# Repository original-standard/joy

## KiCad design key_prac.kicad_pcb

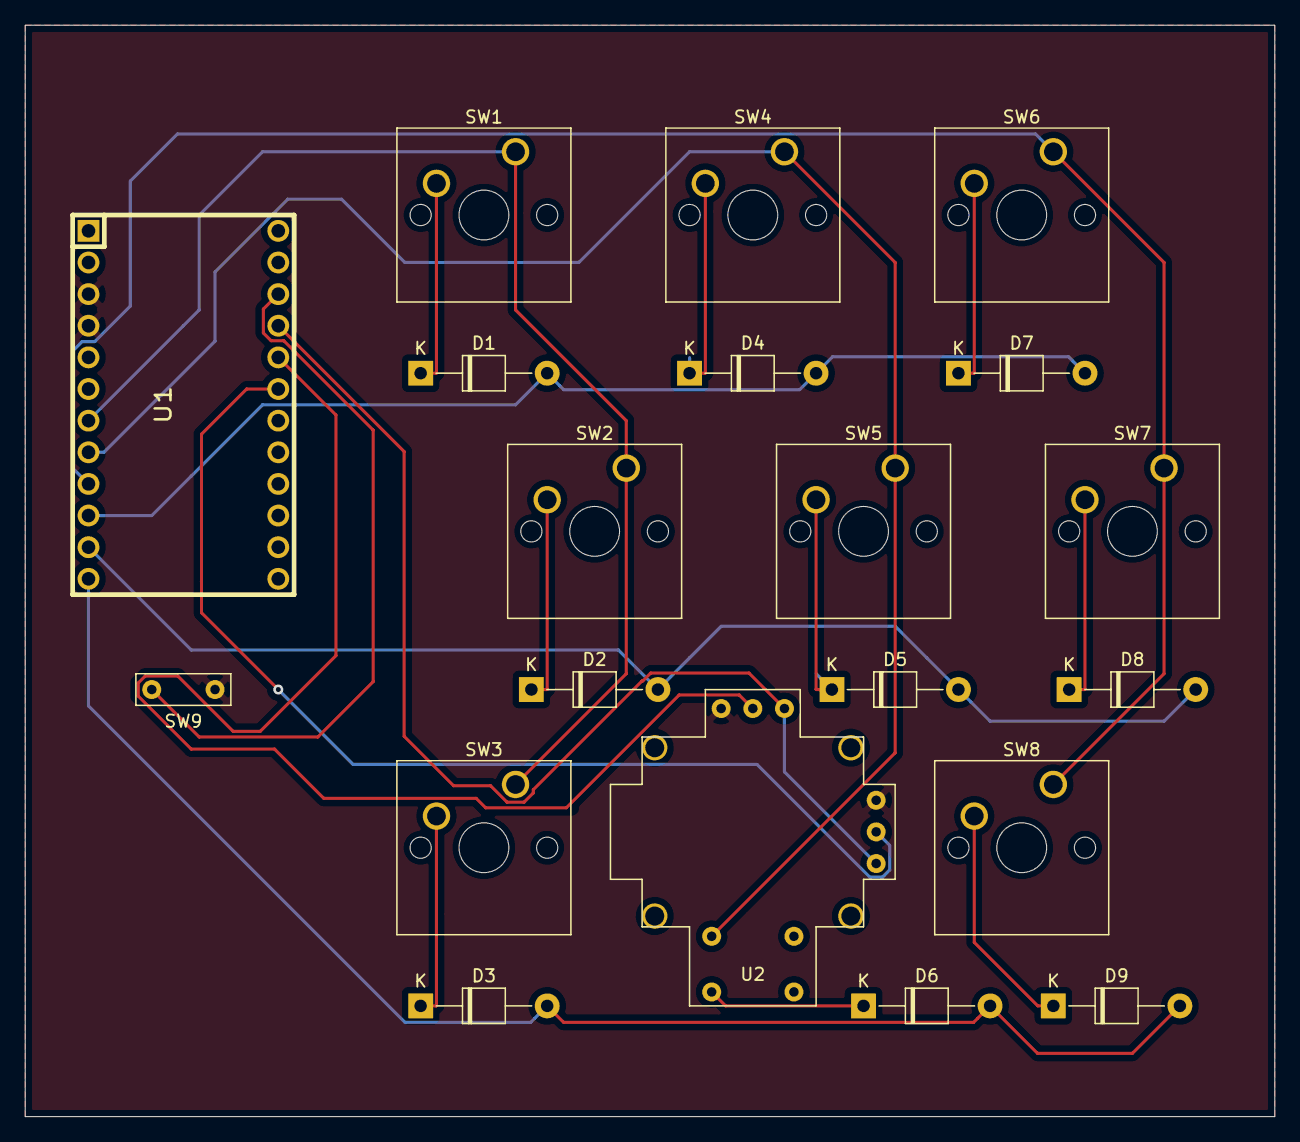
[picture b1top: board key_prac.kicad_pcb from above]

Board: 2 copper layers, 100.3 x 87.6 mm, 20 parts (0 on the bottom side), 20 nets.

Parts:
D1, D2, D3, D4, D5, D6, D7, D8, D9: DIODE; D_T-1_P10.16mm_Horizontal
SW1, SW2, SW3, SW4, SW5, SW6, SW7, SW8: SW_Push; SW_Cherry_MX_1.00u_PCB
SW9: SW_Push; sw
U1: promicro
U2: analog_pad; joypad

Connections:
GND: SW9.2, U1.3, U1.4, U2.1, U2.4
unnamed: D1.1, SW1.2
unnamed: D2.1, SW2.2
unnamed: D3.1, SW3.2
unnamed: D4.1, SW4.2
unnamed: D5.1, SW5.2
unnamed: D7.1, SW6.2
unnamed: D8.1, SW7.2
unnamed: D9.1, SW8.2
unnamed: SW9.1, U1.15
unnamed: U1.16, U2.3, U2.6
unnamed: U1.17, U2.2
unnamed: U1.18, U2.5
col0: SW1.1, SW2.1, SW3.1, U1.7
col1: SW4.1, SW5.1, U1.8, U2.7
col2: SW6.1, SW7.1, SW8.1, U1.9
row0: D1.2, D4.2, D7.2, U1.10
row1: D2.2, D5.2, D8.2, U1.11
row2: D3.2, D6.2, D9.2, U1.12
sw1: D6.1, U2.8

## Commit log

2019-10-22 my first commit
2019-10-31 beta
